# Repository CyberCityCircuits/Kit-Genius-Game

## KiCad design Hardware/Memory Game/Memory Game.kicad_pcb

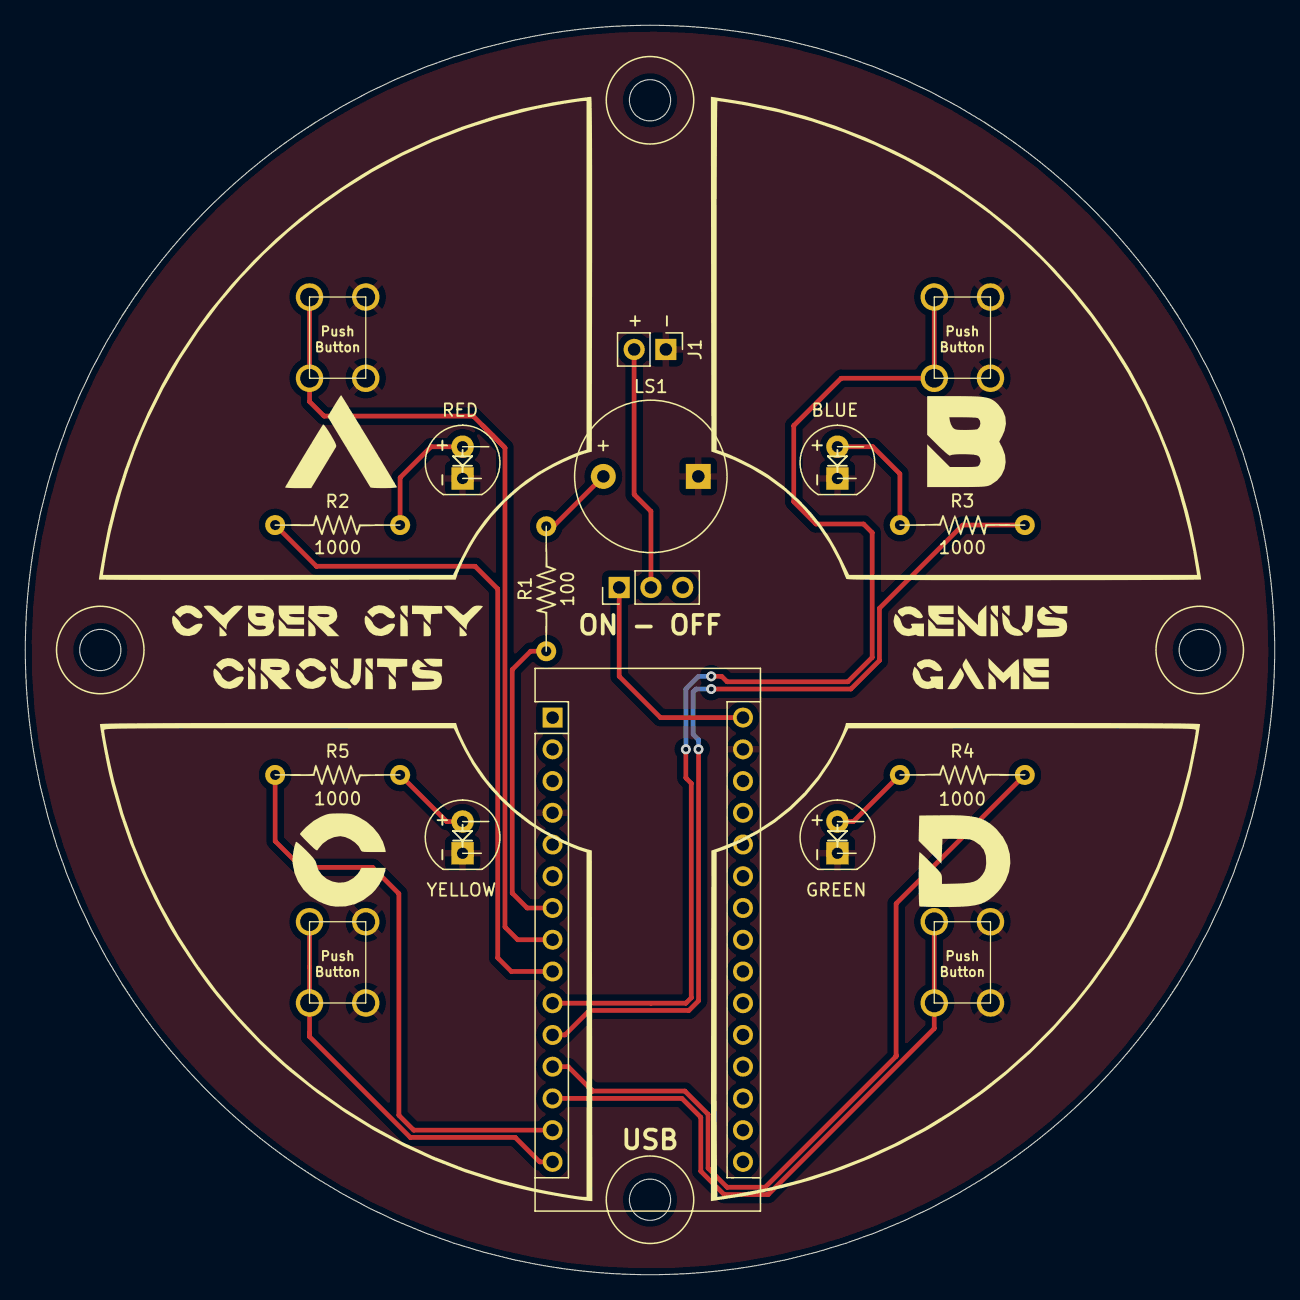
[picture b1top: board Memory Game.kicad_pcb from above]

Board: 2 copper layers, 100.0 x 100.0 mm, 21 parts (0 on the bottom side), 17 nets.

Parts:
 : 3mm_Hole; 3mm Mount Hole
 #2,  #3,  #4: 3mm_Hole; 3mm Mount Hole
A1: Arduino_Nano_v3.x; Arduino_Nano
BLUE: Blue; Schematic - LED 5mm(2.56P) 003
GREEN: Green; Schematic - LED 5mm(2.56P) 003
J1: Battery; 9V_Battery_Terminal
LS1: Speaker; Buzzer_12x9.5RM7.6
R1: 100; Schematic - Resistor 10.00mm
R2, R3, R4, R5: 1000; Schematic - Resistor 10.00mm
RED: Red; Schematic - LED 5mm(2.56P) 003
SW1, SW2, SW3, SW4: SW_Push; Schematic_-_Button_Labeled
SW5: SW_SPDT; PinHeader_1x03_P2.54mm_Vertical
YELLOW: Yellow; Schematic - LED 5mm(2.56P) 003

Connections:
BATTERY: J1.1, SW5.2 (B)
BUTTON_1: A1.8 (D5), SW1.1
BUTTON_2: A1.10 (D7), SW2.1
BUTTON_3: A1.13 (D10), SW3.1
BUTTON_4: A1.15 (D12), SW4.1
GND: A1.4 (GND), A1.29 (GND), BLUE.1 (K), GREEN.1 (K), J1.2, LS1.2, RED.1 (K), SW1.2, SW2.2, SW3.2, SW4.2, YELLOW.1 (K)
LED_1: A1.9 (D6), R2.1
LED_2: A1.11 (D8), R3.1
LED_3: A1.12 (D9), R4.1
LED_4: A1.14 (D11), R5.1
unnamed: R2.2, RED.2 (A)
unnamed: BLUE.2 (A), R3.2
unnamed: GREEN.2 (A), R4.2
unnamed: R5.2, YELLOW.2 (A)
unnamed: LS1.1, R1.2
Speaker: A1.7 (D4), R1.1
VCC: A1.30 (VIN), SW5.1 (A)
